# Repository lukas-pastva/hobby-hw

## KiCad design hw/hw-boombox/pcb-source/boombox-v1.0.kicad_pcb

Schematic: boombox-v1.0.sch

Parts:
F1: Fuse; R_1206
J1: boost; psw-dc-dc-lm2596-HOLE
J2: 5V-BATT; psw-kontakt-smd-velky
J3: GND-BATT; psw-kontakt-smd-velky
J4: charger; psw-charger-18650-usb-c
J5: amp; psw-d-class-amp-bluetooth
SW1: SW_DIP_x01; psw-switch-240V

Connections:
unnamed: F1.1, F1.2, J2.1, J4.3, SW1.2
unnamed: J1.1, SW1.1
unnamed: J1.2, J3.1, J4.4
unnamed: J1.3, J5.2
unnamed: J1.4, J5.1

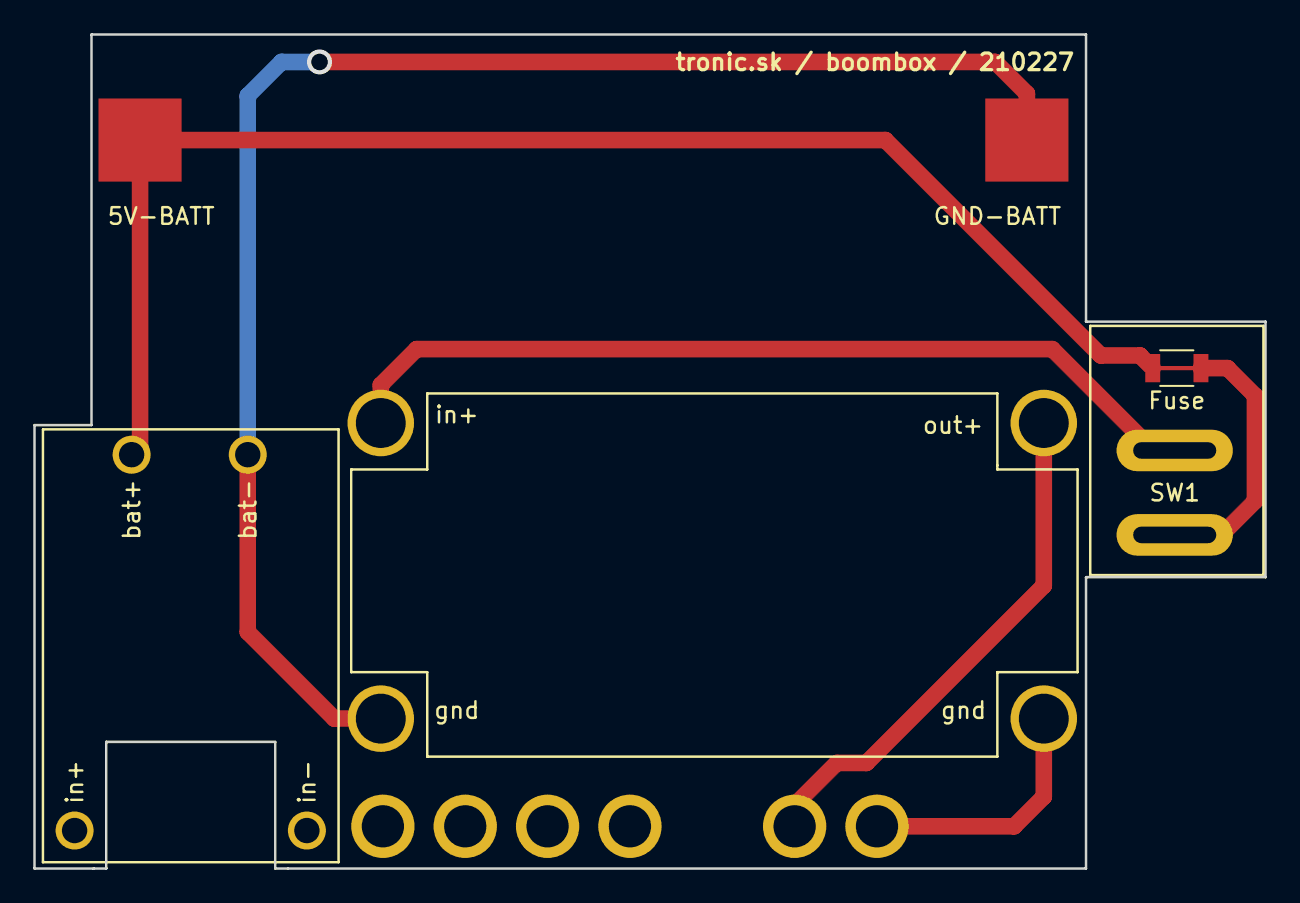
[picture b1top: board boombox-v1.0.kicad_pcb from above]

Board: 2 copper layers, 74.0 x 50.2 mm, 7 parts (1 on the bottom side), 5 nets.

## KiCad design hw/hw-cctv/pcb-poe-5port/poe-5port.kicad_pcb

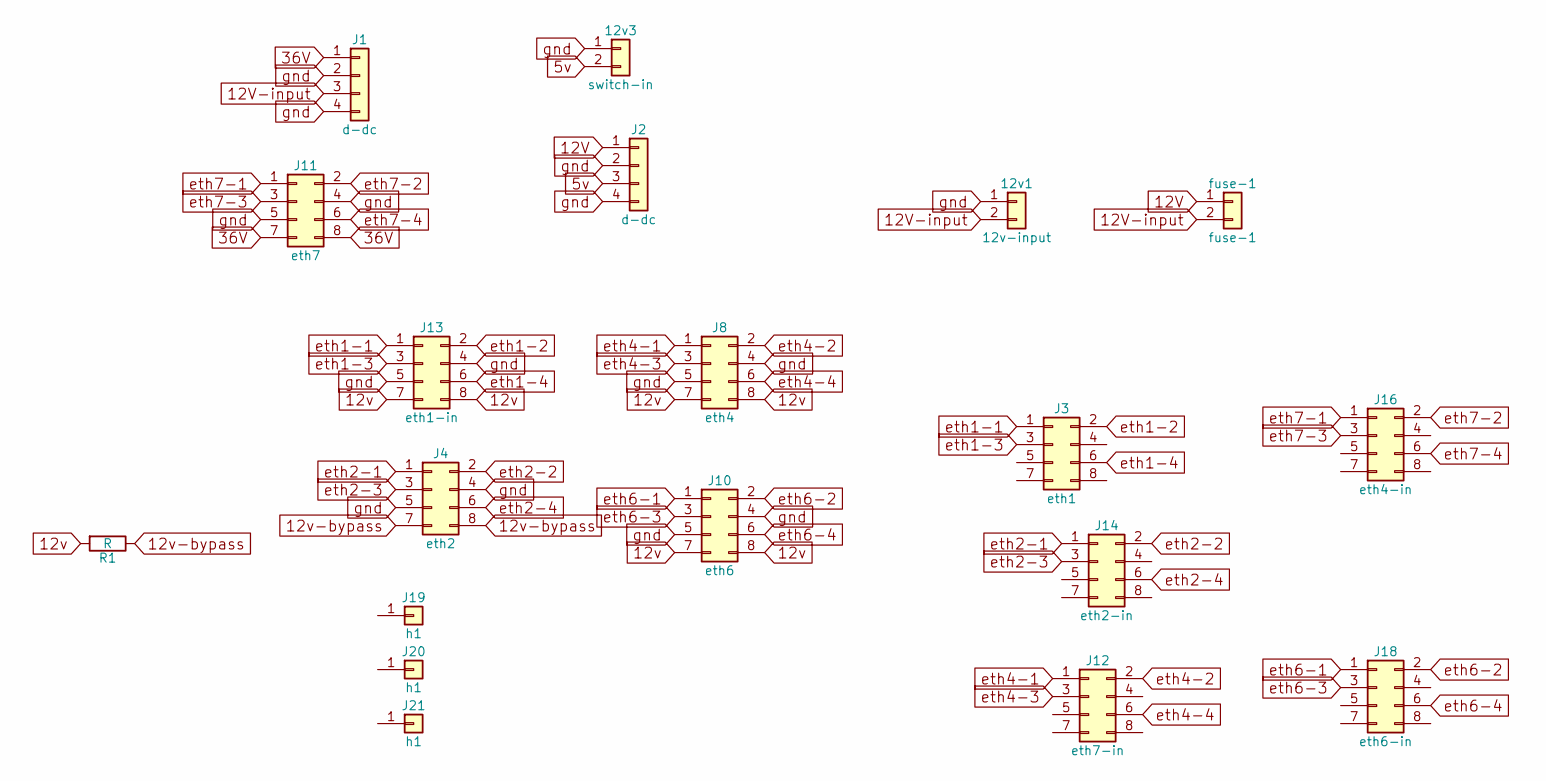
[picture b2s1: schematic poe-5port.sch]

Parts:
12v1: 12v-input; psw-konektor-zeleny
12v3: switch-in; psw-konektor-zeleny
J1, J2: d-dc; psw-dc-dc-lm2596
J3: eth1; psw-rj-45-switch
J4: eth2; psw-rj45-no-hole
J8: eth4; psw-rj45-no-hole
J10: eth6; psw-rj45-no-hole
J11: eth7; psw-rj45-no-hole
J12: eth7-in; psw-rj-45-switch
J13: eth1-in; psw-rj45-no-hole
J14: eth2-in; psw-rj-45-switch
J16: eth4-in; psw-rj-45-switch
J18: eth6-in; psw-rj-45-switch
J19, J20, J21: h1; MountingHole_3mm_Pad
R1: R; tlacitko
fuse-1: fuse-1; psw-poistka-auto

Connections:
5v: 12v3.2, J2.3
12V: J2.1, J8.7, J8.8, J10.7, J10.8, J13.7, J13.8, R1.2, fuse-1.1
12V-input: 12v1.2, J1.3, fuse-1.2
12v-bypass: J4.7, J4.8, R1.1
36V: J1.1, J11.7, J11.8
unnamed 5: J19.1; also elsewhere on the board
eth1-1: J3.1, J13.1
eth1-2: J3.2, J13.2
eth1-3: J3.3, J13.3
eth1-4: J3.6, J13.6
eth2-1: J4.1, J14.1
eth2-2: J4.2, J14.2
eth2-3: J4.3, J14.3
eth2-4: J4.6, J14.6
eth4-1: J8.1, J12.1
eth4-2: J8.2, J12.2
eth4-3: J8.3, J12.3
eth4-4: J8.6, J12.6
eth6-1: J10.1, J18.1
eth6-2: J10.2, J18.2
eth6-3: J10.3, J18.3
eth6-4: J10.6, J18.6
eth7-1: J11.1, J16.1
eth7-2: J11.2, J16.2
eth7-3: J11.3, J16.3
eth7-4: J11.6, J16.6
gnd: 12v1.1, 12v3.1, J1.2, J1.4, J2.2, J2.4, J4.4, J4.5, J8.4, J8.5, J10.4, J10.5, J11.4, J11.5, J13.4, J13.5

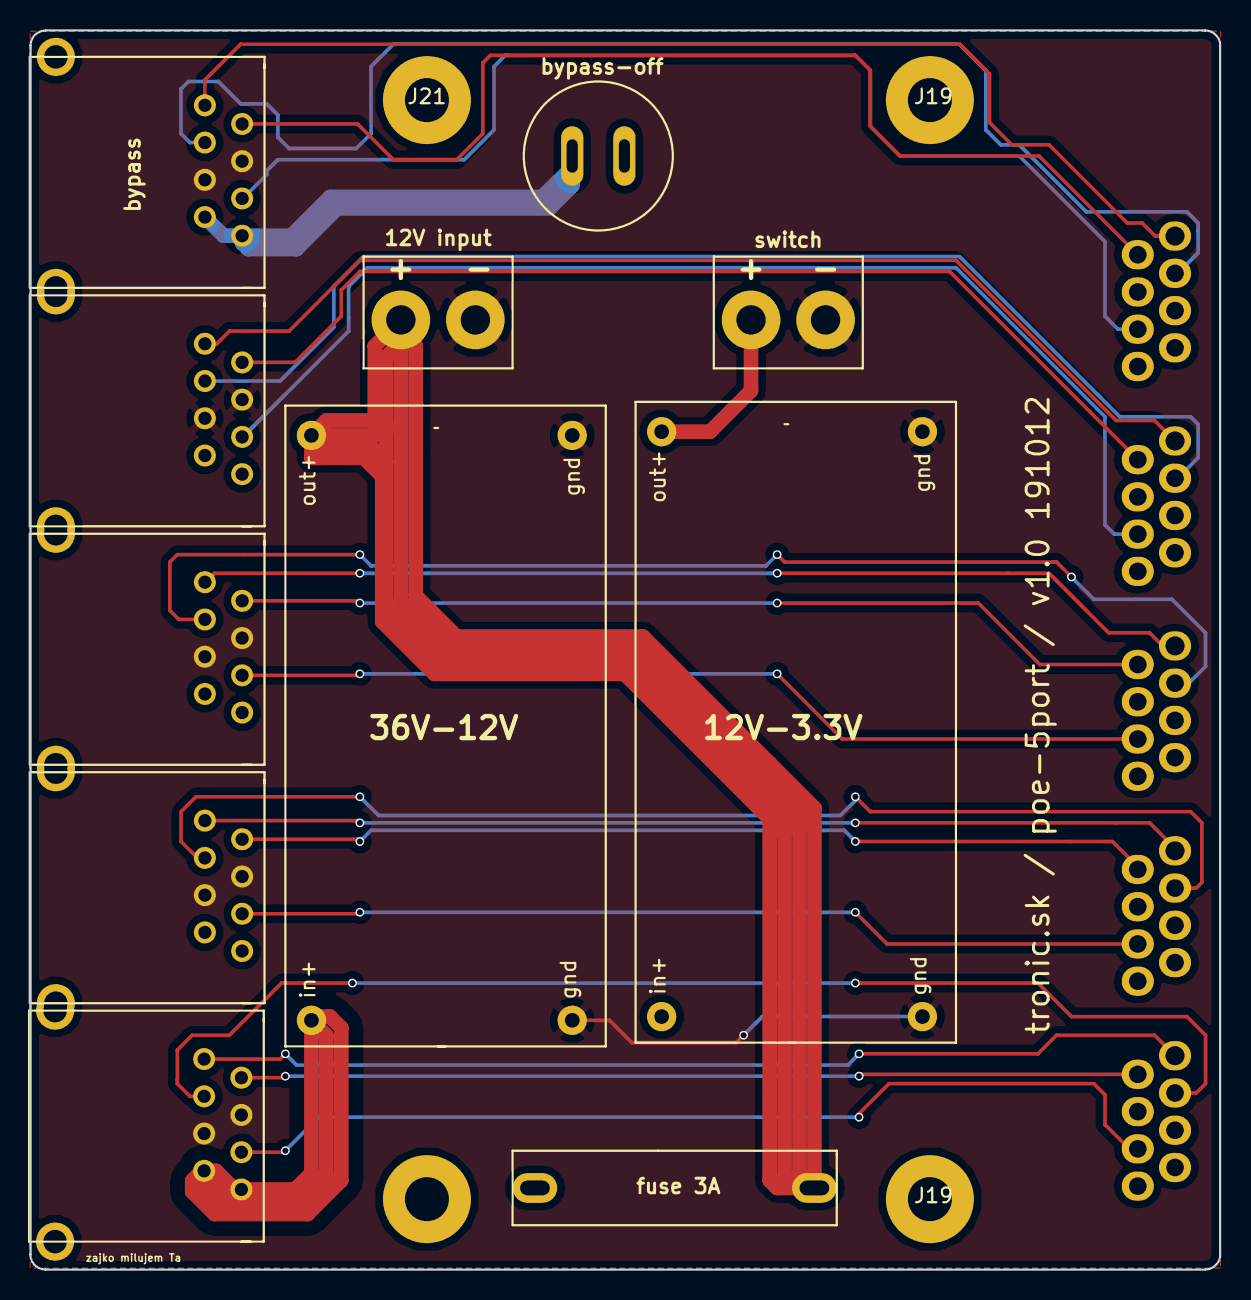
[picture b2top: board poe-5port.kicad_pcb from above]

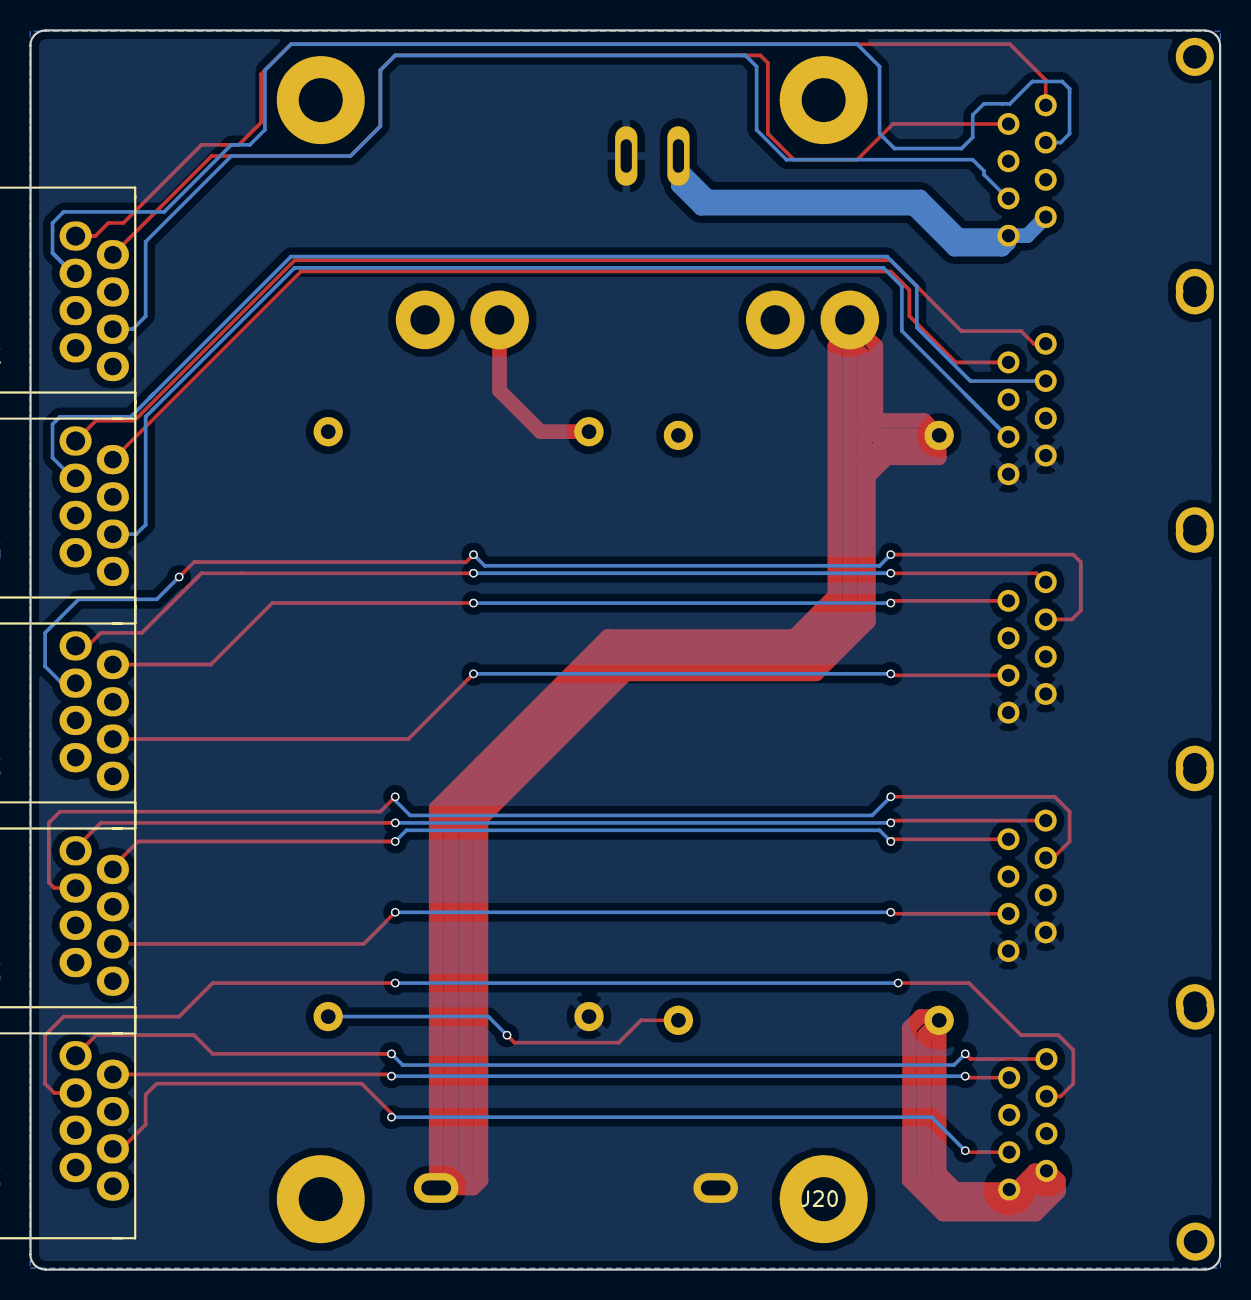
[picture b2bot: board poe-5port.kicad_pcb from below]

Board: 2 copper layers, 81.1 x 84.5 mm, 20 parts (6 on the bottom side), 27 nets.

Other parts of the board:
J19#2: h1; MountingHole_3mm_Pad

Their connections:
unnamed 5: J19#2.1; also elsewhere on the board

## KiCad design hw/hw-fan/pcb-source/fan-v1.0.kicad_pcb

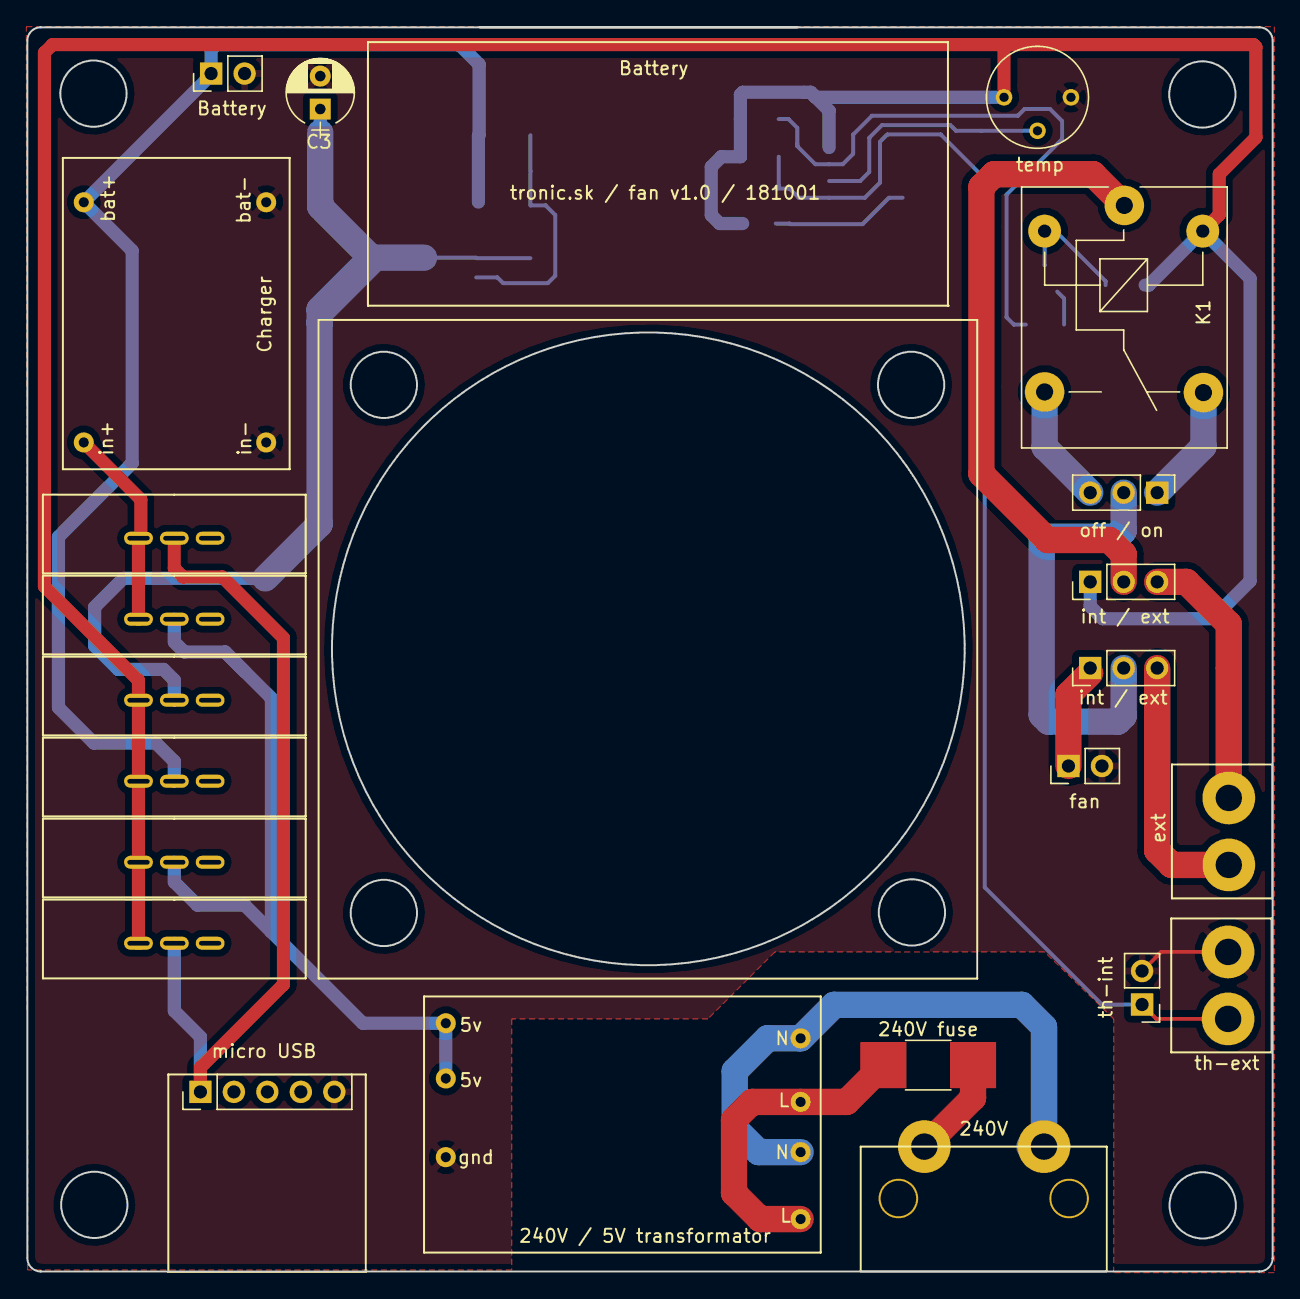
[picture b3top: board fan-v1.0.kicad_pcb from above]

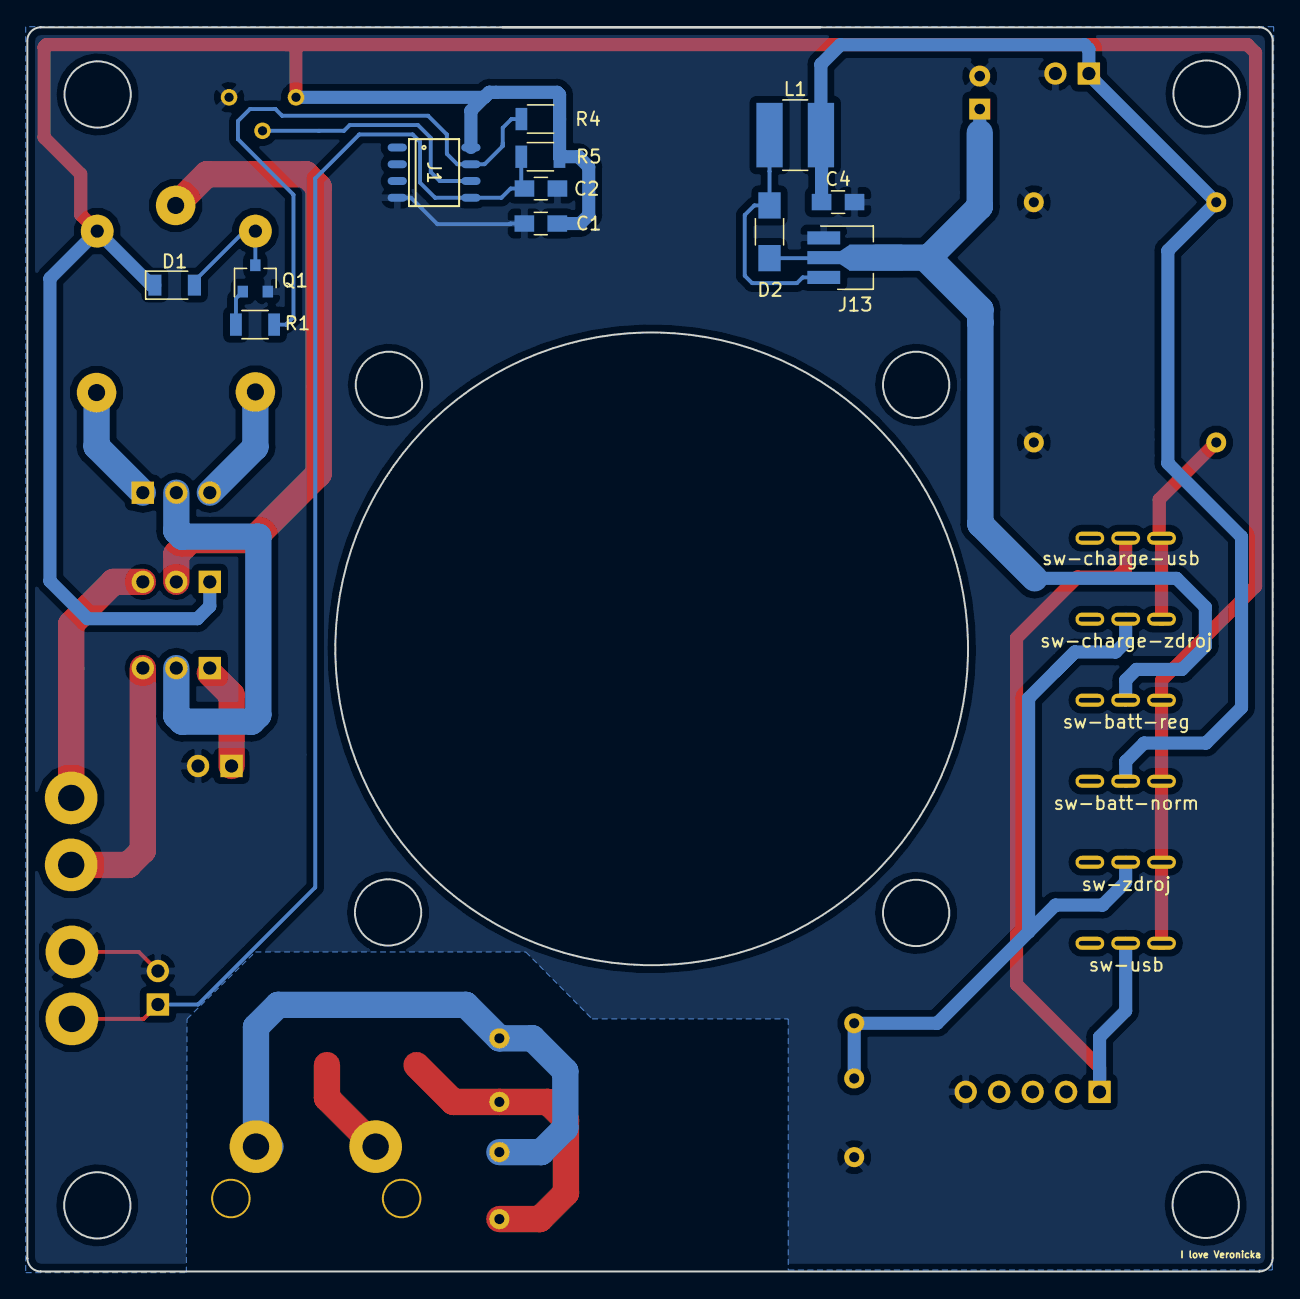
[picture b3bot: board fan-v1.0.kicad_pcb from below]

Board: 2 copper layers, 94.5 x 94.4 mm, 34 parts (12 on the bottom side), 23 nets.

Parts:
240V: 240V; 240v-c8
240V / 5V transformator: Zdroj; 5v-zdroj-dual
240V fuse: Fuse; R_1812_HandSoldering
Battery: batt; Pin_Header_Straight_1x02_Pitch2.54mm
C1, C2, C4: C; C_0805_HandSoldering
C3: CP1; CP_Radial_D5.0mm_P2.50mm
Charger: charger; psw-lipo-nabijacka
D1: D; D_1206
D2: D_Zener; R_1206_HandSoldering
J1: lm393; SO-8
J13: e50p; SOT-89-3_Handsoldering
K1: G5LE-1; Relay_SPDT_SANYOU_SRD_Series_Form_C
L1: INDUCTOR; R_1218_HandSoldering
Q1: PN2222A; SOT-23
R1, R4, R5: R; R_1206
ext: bypass; psw-konektor-zeleny
fan: fan; Pin_Header_Straight_1x02_Pitch2.54mm
int / ext: int-ext-in; Pin_Header_Straight_1x03_Pitch2.54mm
int / ext#2: int-ext-out; Pin_Header_Straight_1x03_Pitch2.54mm
micro USB: micro-usb; Pin_Header_Straight_1x05_Pitch2.54mm
off / on: on-off; Pin_Header_Straight_1x03_Pitch2.54mm
sw-batt-norm: sw-batt-norm; psw-vypinac-maly-trojity
sw-batt-reg: sw-batt-reg; psw-vypinac-maly-trojity
sw-charge-usb: sw-charge-usb; psw-vypinac-maly-trojity
sw-charge-zdroj: sw-charge-zdroj; psw-vypinac-maly-trojity
sw-usb: sw-usb; psw-vypinac-maly-trojity
sw-zdroj: sw-zdroj; psw-vypinac-maly-trojity
temp: R_POT; Potentiometer_Trimmer_Bourns_3339P_Horizontal
th-ext: therm; psw-konektor-zeleny
th-int: Therm; Pin_Header_Straight_1x02_Pitch2.54mm

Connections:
5v: C1.1, D1.1, J1.8, K1.5, R4.1, R5.1, int / ext.1, sw-batt-norm.1, sw-batt-reg.1, sw-usb.1, sw-zdroj.1, temp.3
5vbatt: Battery.1, C4.1, Charger.3, L1.2, sw-batt-norm.2
5vbatt-charge: Charger.1, sw-charge-usb.1, sw-charge-zdroj.1
5vbatt-regulated: C3.1, D2.1, J13.2, sw-batt-reg.2
unnamed: D1.2, K1.2, Q1.3
unnamed: D2.2, J13.3, L1.1
unnamed: 240V / 5V transformator.1, 240V fuse.1
unnamed: 240V.2, 240V fuse.2
unnamed: 240V.1, 240V / 5V transformator.2
unnamed: 240V / 5V transformator.3, sw-charge-zdroj.2, sw-zdroj.2
unnamed: micro USB.1, sw-charge-usb.2, sw-usb.2
unnamed: K1.1, int / ext.2
unnamed: K1.4, off / on.1
unnamed: K1.3, off / on.3
unnamed: Q1.1, R1.2
fan-in: fan.1, int / ext#2.1
gnd: 240V / 5V transformator.4, Battery.2, C1.2, C2.2, C3.2, C4.2, Charger.2, Charger.4, J1.4, J13.1, Q1.2, fan.2, micro USB.5, temp.1, th-ext.1, th-int.2
in2+: C2.1, J1.5, R5.2, th-ext.2, th-int.1
in2-: J1.6, temp.2
input: ext.1, int / ext.3
out: J1.7, R1.1, R4.2
output: ext.2, int / ext#2.3
relay-out: int / ext#2.2, off / on.2

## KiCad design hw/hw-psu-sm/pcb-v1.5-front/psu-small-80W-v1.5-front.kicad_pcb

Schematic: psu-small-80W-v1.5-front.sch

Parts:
+1: +; psw-bananik
-1: -; psw-bananik
J9, J10: pot-1; psw-pot-through-horizontal
J12, J13, J14, J15: srobik; psw-srobik-3.5mm
R1, R2: R; R_1206
conn1: Conn_02x10_Odd_Even; Pin_Header_Straight_2x10_Pitch2.54mm_SMD
gnd-out1: gnd-out; psw-kontakt-smd-velky
zem1: zem; psw-kontakt-smd-velky

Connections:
12v-reg: +1.1, conn1.7, conn1.8, conn1.9, conn1.10, conn1.11, conn1.12, conn1.13, conn1.14, conn1.15, conn1.16
unnamed: J9.1, R1.1, conn1.5
unnamed: J9.2, conn1.3
unnamed: J9.3, R1.2, conn1.1
unnamed: J10.1, R2.2, conn1.6
unnamed: J10.2, conn1.4
unnamed: J10.3, R2.1, conn1.2
gnd-out: -1.1, gnd-out1.1
zem: J12.1, J13.1, J14.1, J15.1, zem1.1

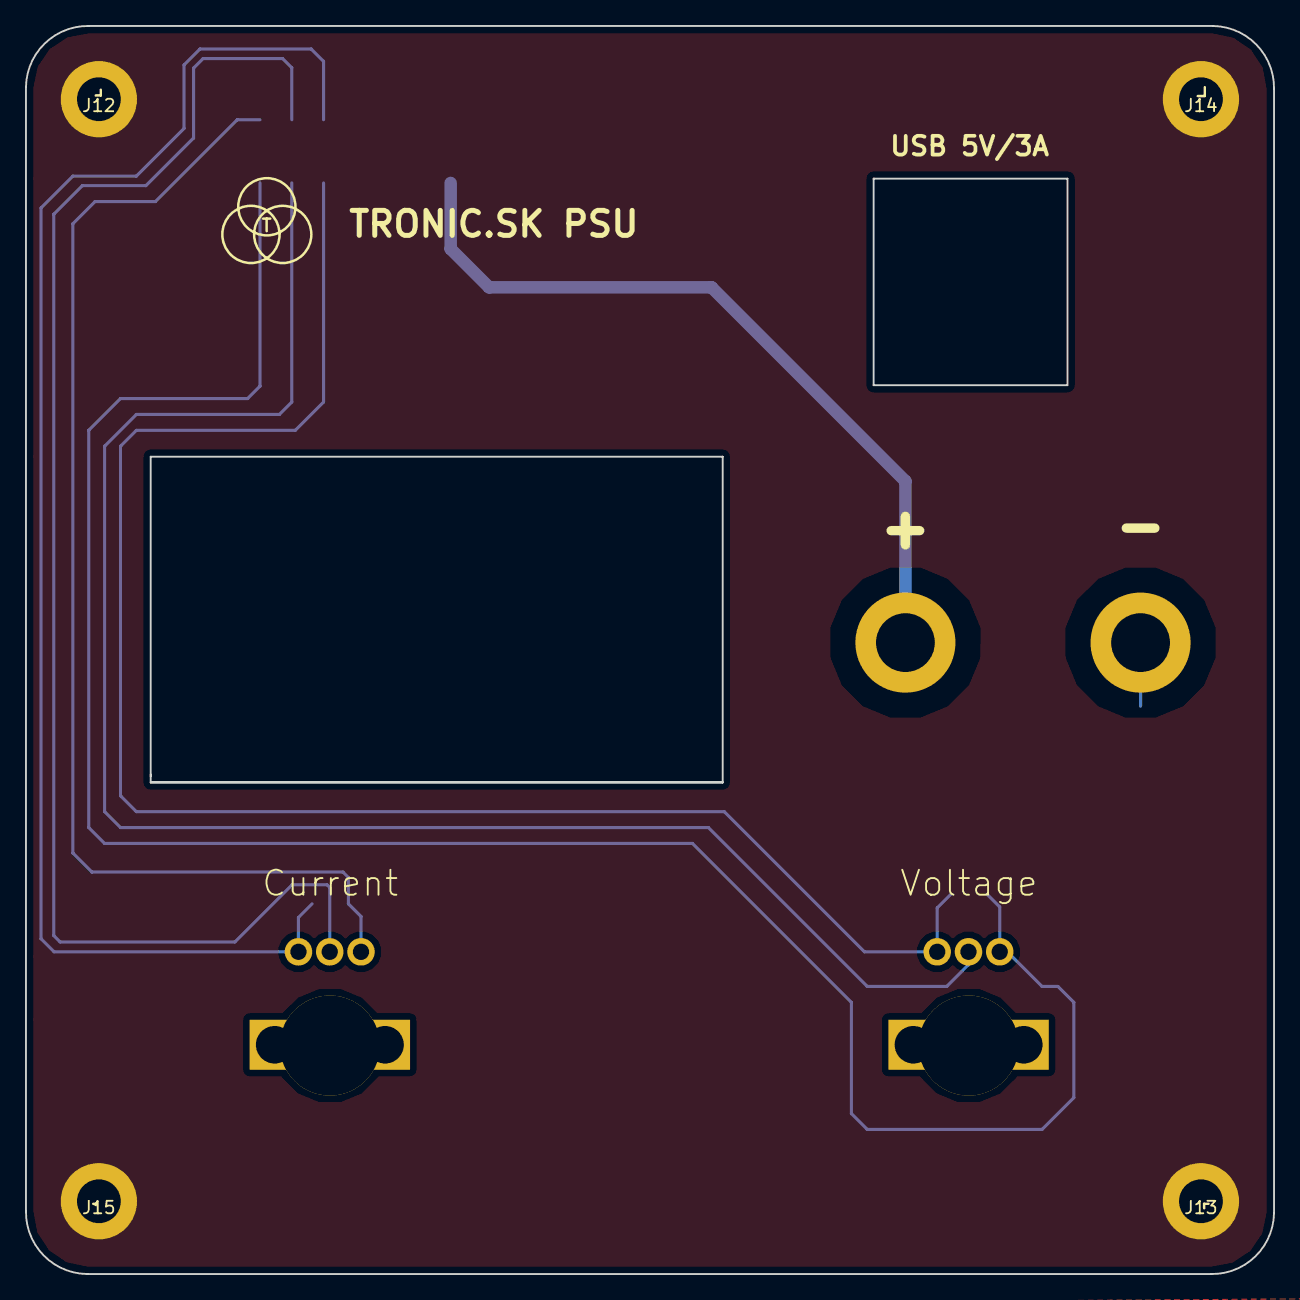
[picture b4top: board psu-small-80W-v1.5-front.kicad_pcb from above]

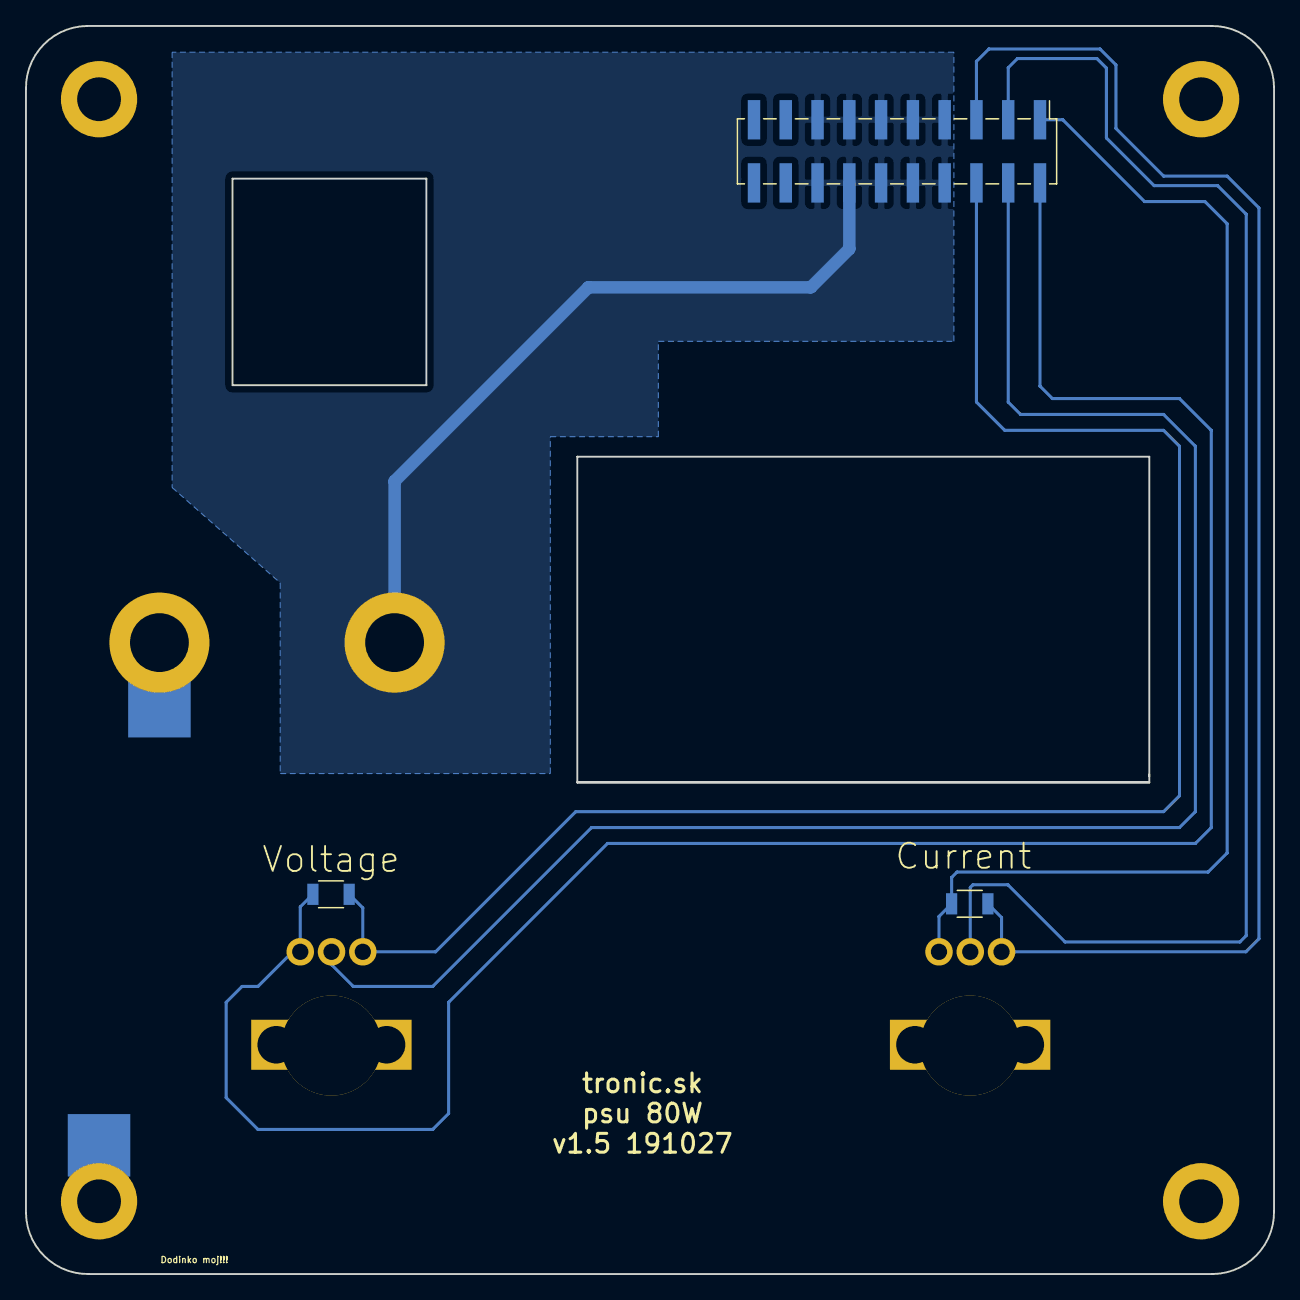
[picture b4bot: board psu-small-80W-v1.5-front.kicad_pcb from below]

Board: 2 copper layers, 99.8 x 99.8 mm, 13 parts (5 on the bottom side), 9 nets.

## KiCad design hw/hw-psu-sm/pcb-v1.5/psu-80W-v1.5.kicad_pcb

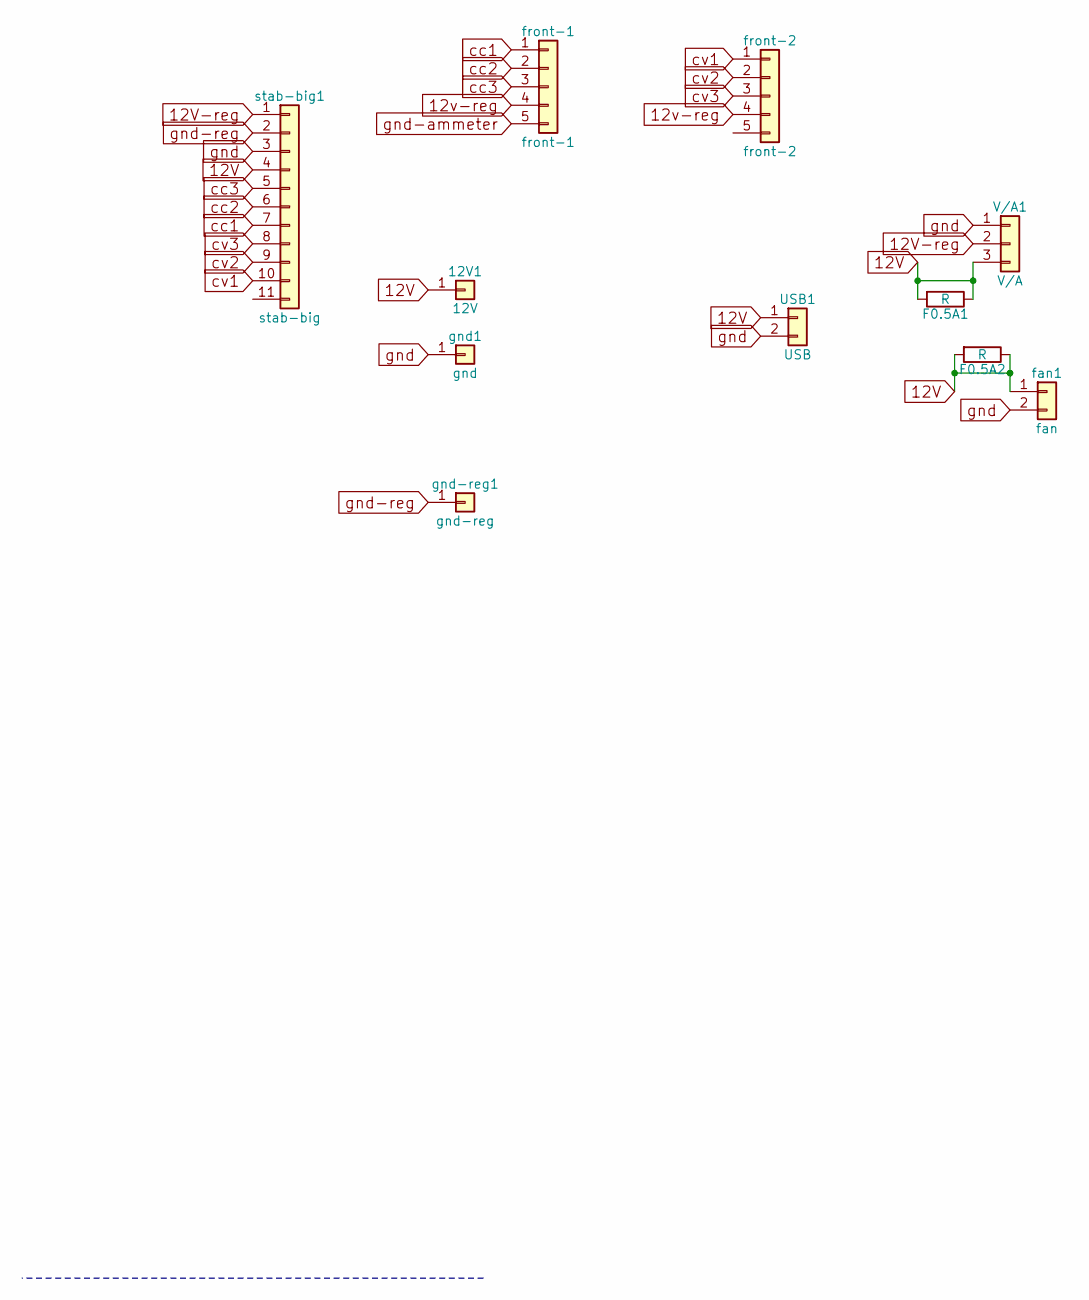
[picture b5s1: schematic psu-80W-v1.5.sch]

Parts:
12V1: 12V; MountingHole_3.2mm_M3_Pad_Via
F0.5A1, F0.5A2: R; R_1206
USB1: USB; psw-usb-charger-double
V/A1: V/A; Pin_Header_Straight_1x03_Pitch2.54mm
fan1: fan; Pin_Header_Straight_1x02_Pitch2.54mm
front-1: front-1; psw-conn-regulators
front-2: front-2; psw-conn-regulators
gnd1: gnd; MountingHole_3.2mm_M3_Pad_Via
gnd-reg1: gnd-reg; MountingHole_3.2mm_M3_Pad_Via
stab-big1: stab-big; psw-reg-big-buck-boost

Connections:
12V: 12V1.1, F0.5A1.1, F0.5A1.2, F0.5A2.1, F0.5A2.2, USB1.1, V/A1.3, fan1.1, stab-big1.4
12V-reg: V/A1.2, front-1.4, front-2.4, stab-big1.1
cc1: front-1.1, stab-big1.7
cc2: front-1.2, stab-big1.6
cc3: front-1.3, stab-big1.5
cv1: front-2.1, stab-big1.10
cv2: front-2.2, stab-big1.9
cv3: front-2.3, stab-big1.8
gnd: USB1.2, V/A1.1, fan1.2, gnd1.1, stab-big1.3
gnd-ammeter: front-1.5
gnd-reg: gnd-reg1.1, stab-big1.2

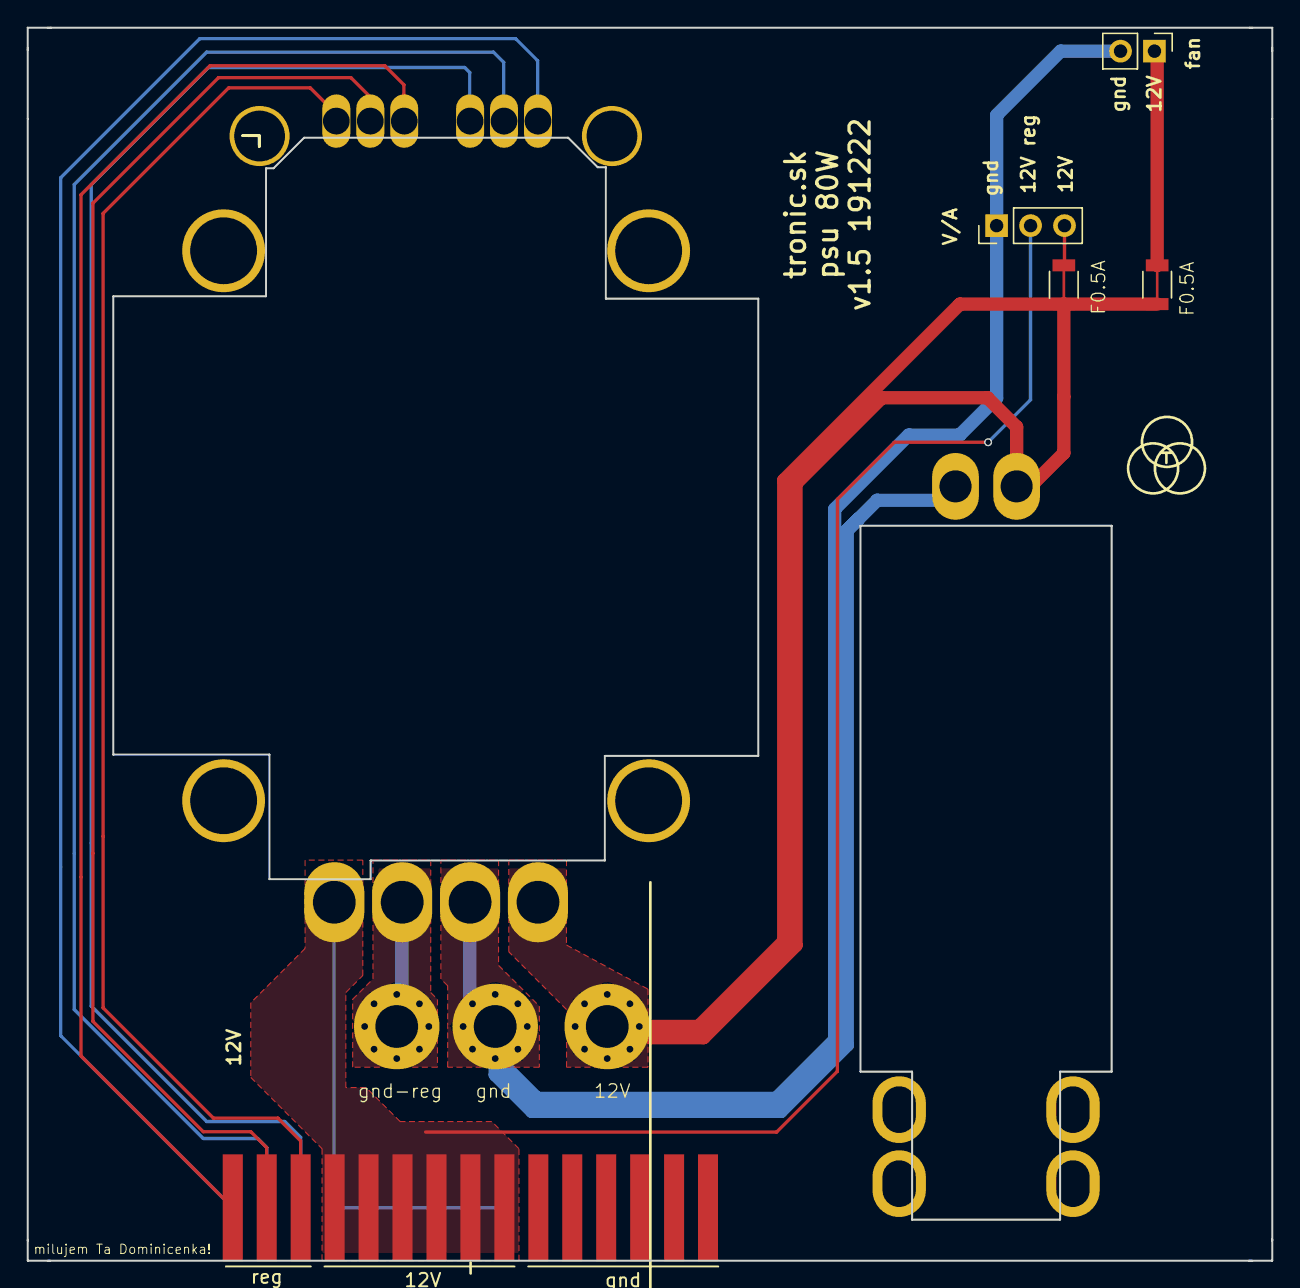
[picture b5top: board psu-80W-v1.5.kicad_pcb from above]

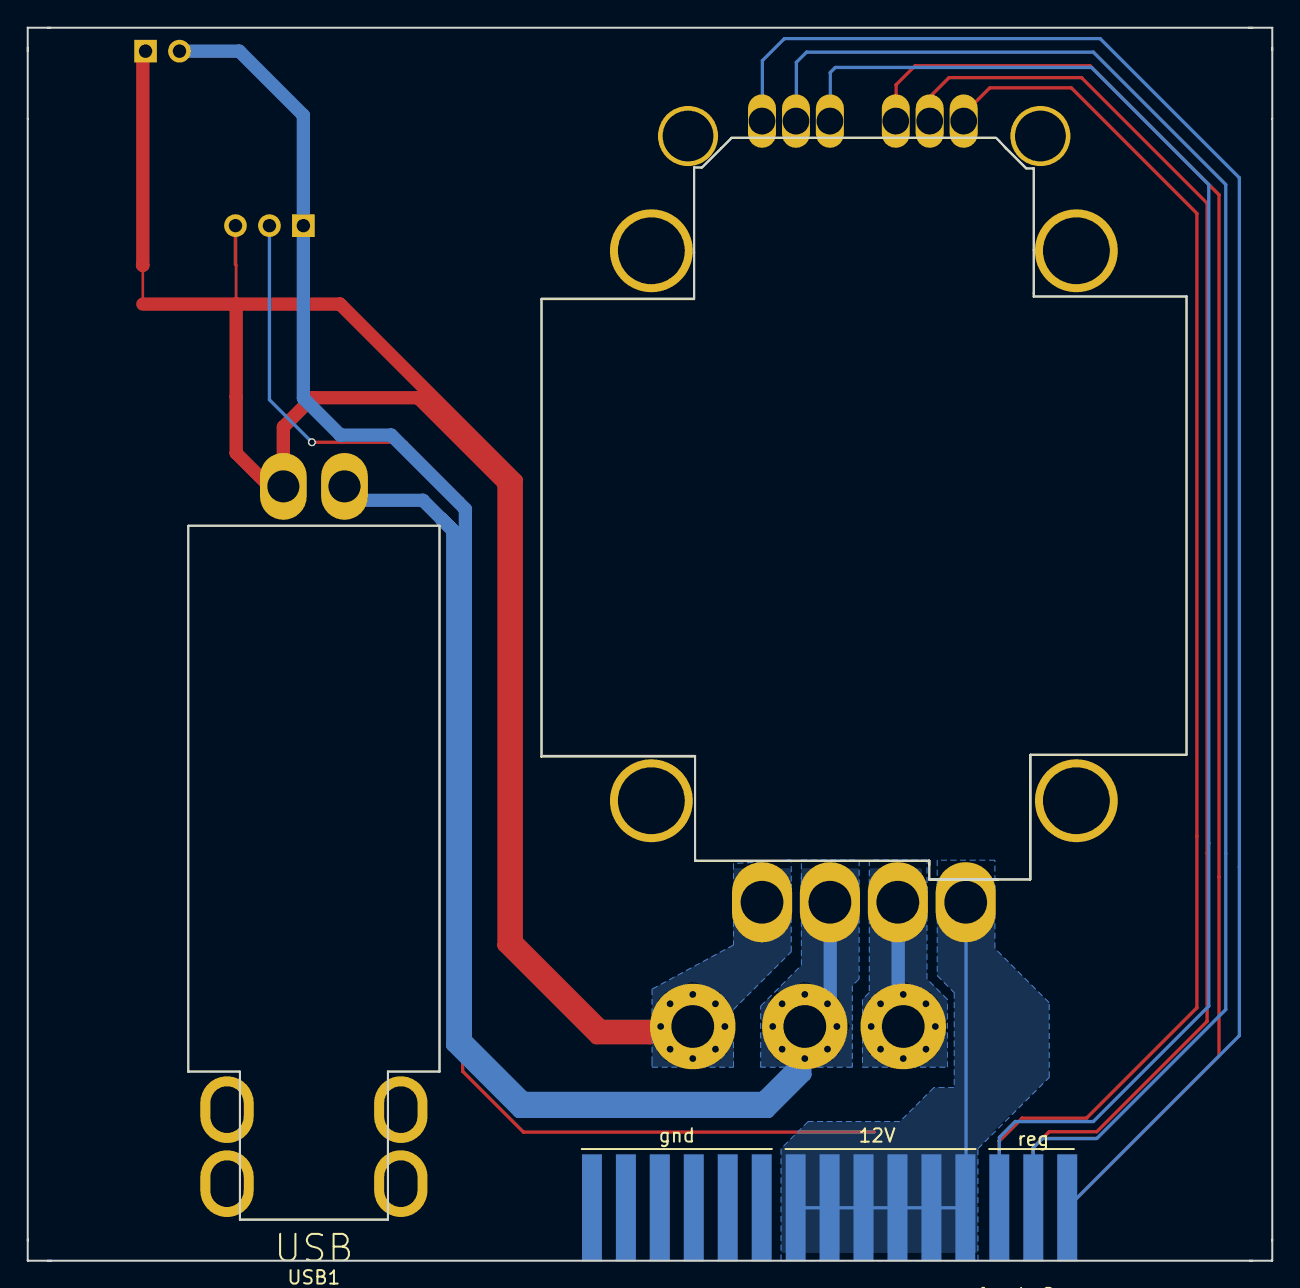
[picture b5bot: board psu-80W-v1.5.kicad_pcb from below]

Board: 2 copper layers, 93.1 x 92.3 mm, 11 parts (3 on the bottom side), 10 nets.
